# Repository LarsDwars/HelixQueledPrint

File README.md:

# HelixQueledPrint
An break out board and LED driver for RGBW LED's from the showtec helix s5000 or any queled Q4xx light

yay

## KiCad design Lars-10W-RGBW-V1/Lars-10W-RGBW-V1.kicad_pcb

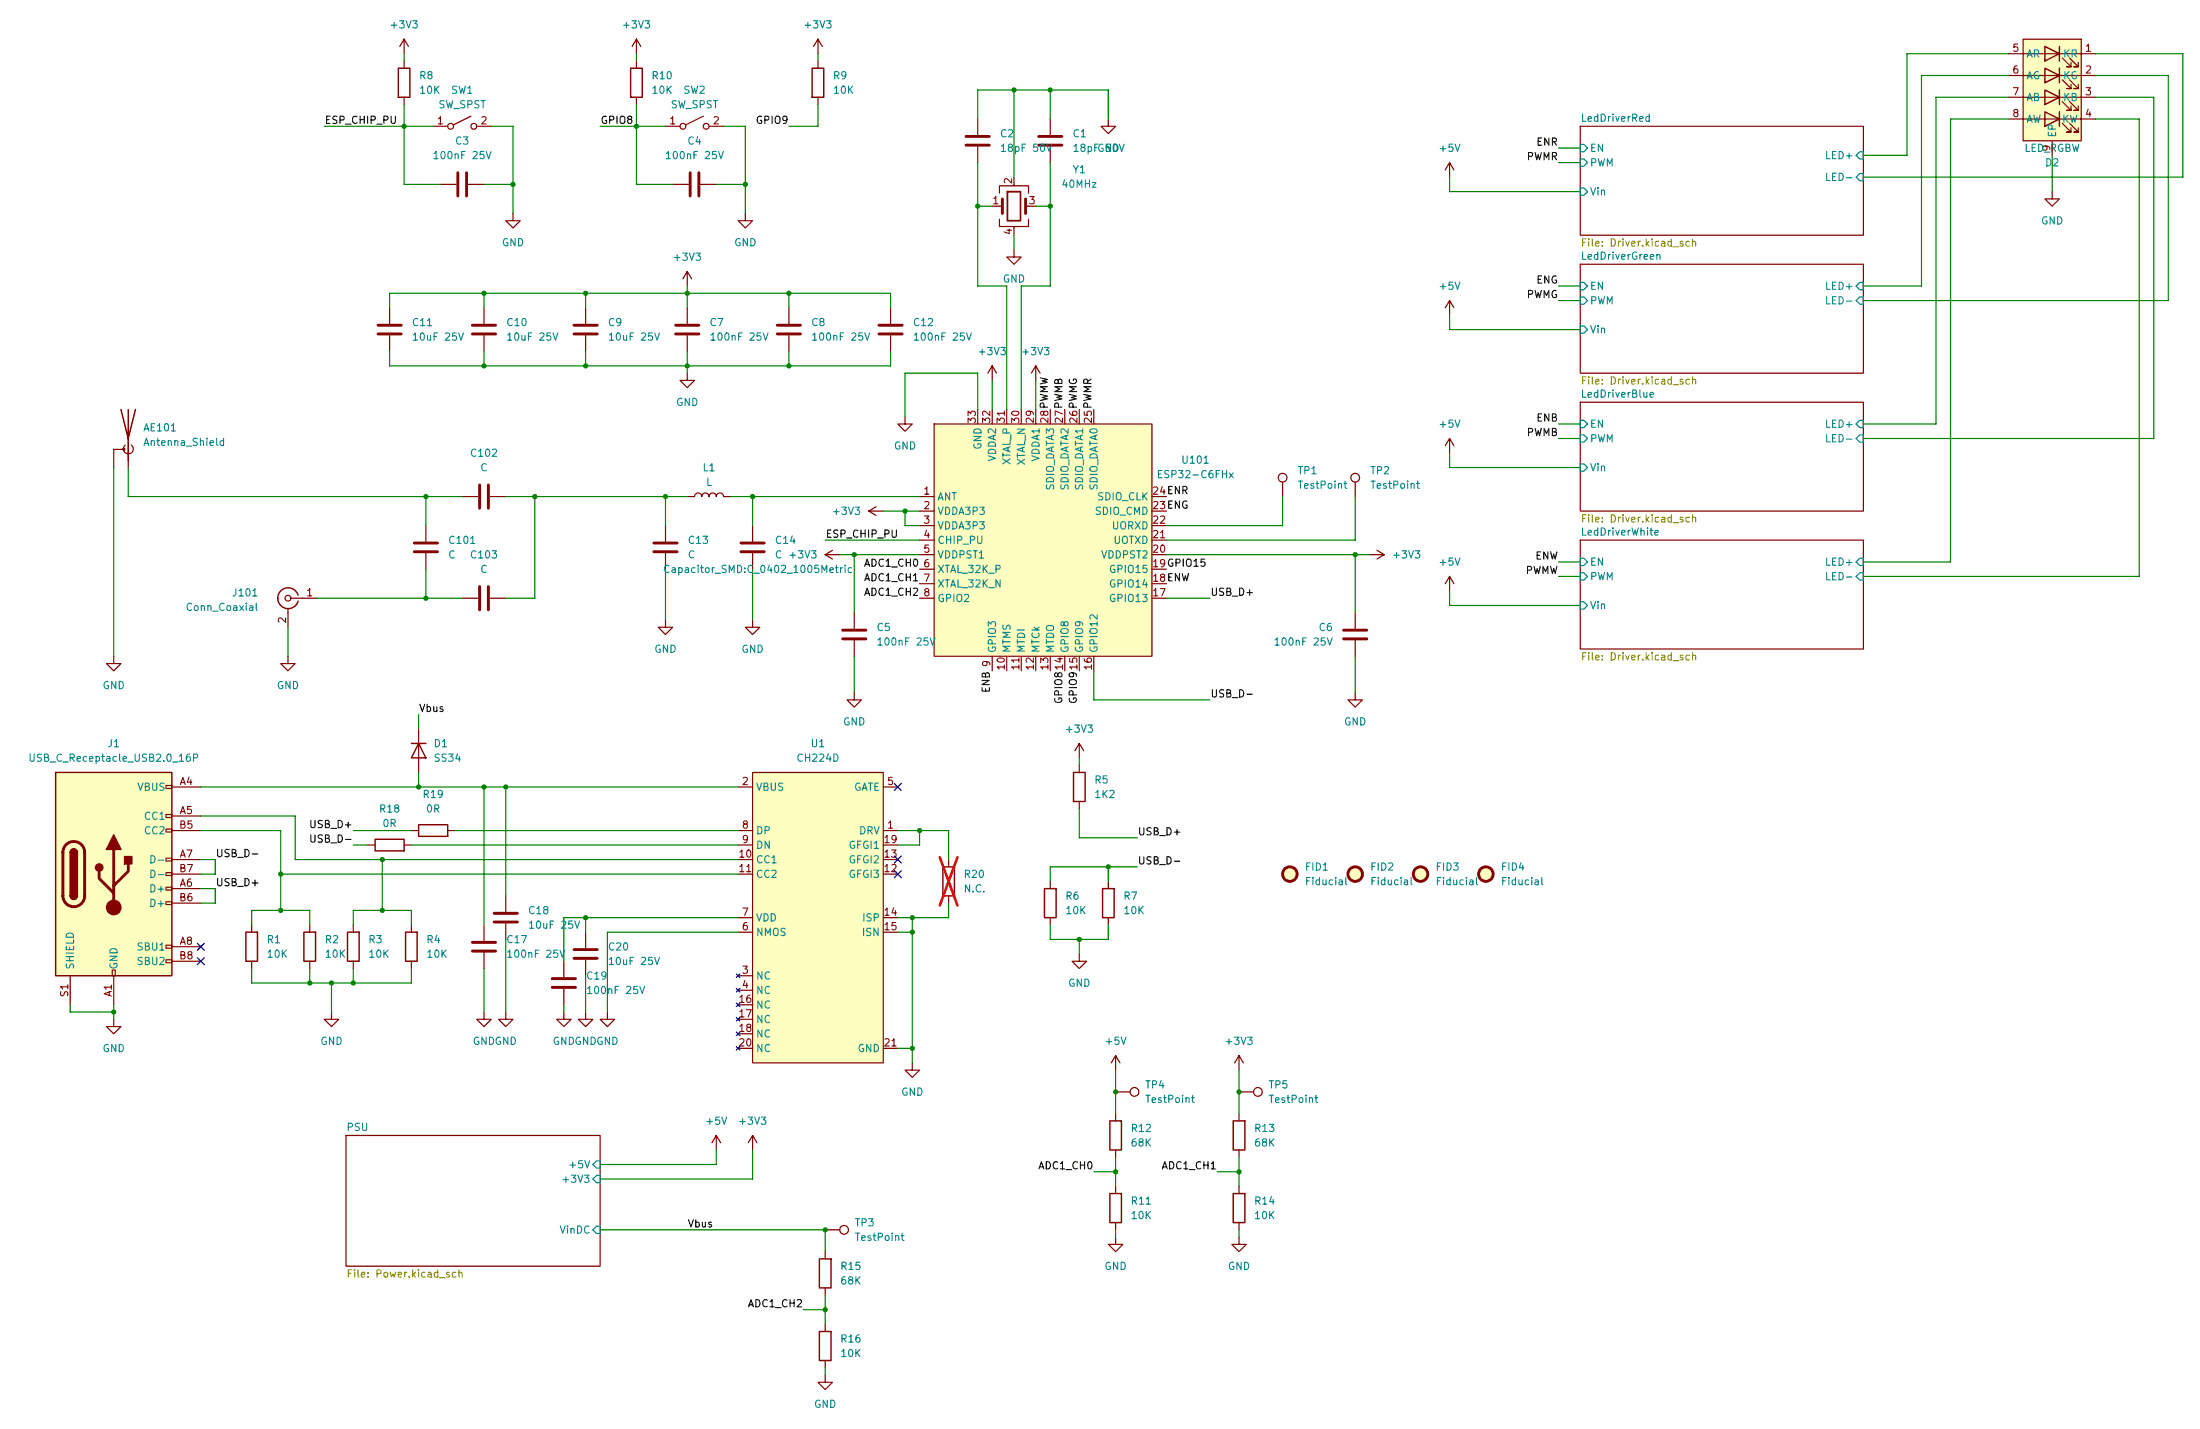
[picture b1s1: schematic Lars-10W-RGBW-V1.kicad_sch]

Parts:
AE101: Antenna_Shield; Texas_SWRA117D_2.4GHz_Right
C1, C2: 18pF 50V; C_0402_1005Metric
C3, C4, C5, C6, C7, C8, C12, C17, C19: 100nF 25V; C_0402_1005Metric
C9, C10, C11, C18, C20: 10uF 25V; C_0805_2012Metric
C13, C14, C101, C102, C103: C; C_0402_1005Metric
D1: SS34; SMA; MPN SS34
D2: LED_RGBW; QR4xLED
FID1, FID2, FID3, FID4: Fiducial; FIDUCIAL_Diameter_1mm
J1: USB_C_Receptacle_USB2.0_16P; USB_C_Receptacle_GCT_USB4105-xx-A_16P_TopMnt_Horizontal
J101: Conn_Coaxial; U.FL_Hirose_U.FL-R-SMT-1_Vertical; MPN RF1-2626-125CE-CT
L1: L; L_0402_1005Metric
R1, R2, R3, R4, R6, R7, R8, R9, R10, R11, R14, R16: 10K; R_0402_1005Metric
R5: 1K2; R_0402_1005Metric
R12, R13, R15: 68K; R_0402_1005Metric
R18, R19: 0R; R_0402_1005Metric
R20: N.C.; R_0402_1005Metric; not fitted
SW1, SW2: SW_SPST; TS1101A26025; MPN GT-TC034A-H025-L1NB
TP1, TP2, TP3, TP4, TP5: TestPoint; TestPoint_Pad_D1.0mm
U1: CH224D; QFN-20-1EP_3x3mm_P0.4mm_EP1.65x1.65mm_ThermalVias
U101: ESP32-C6FHx; QFN-32-1EP_5x5mm_P0.5mm_EP3.65x3.65mm_ThermalVias
Y1: 40MHz; Crystal_SMD_3225-4Pin_3.2x2.5mm_HandSoldering; MPN C37635388

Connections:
+3V3: C5.1, C6.1, C7.1, C8.1, C9.1, C10.1, C11.1, C12.1, R5.1, R8.1, R9.1, R10.1, R13.2, TP5.1, U101.2 (VDDA3P3), U101.3 (VDDA3P3), U101.5 (VDDPST1), U101.20 (VDDPST2), U101.29 (VDDA1), U101.32 (VDDA2); also elsewhere on the board
+5V: R12.2, TP4.1; also elsewhere on the board
/ADC1_CH0: R11.2, R12.1, U101.6 (XTAL_32K_P)
/ADC1_CH1: R13.1, R14.2, U101.7 (XTAL_32K_N)
/ADC1_CH2: R15.1, R16.2, U101.8 (GPIO2)
/ENB: U101.9 (GPIO3); also elsewhere on the board
/ENG: U101.23 (SDIO_CMD); also elsewhere on the board
/ENR: U101.24 (SDIO_CLK); also elsewhere on the board
/ENW: U101.18 (GPIO14); also elsewhere on the board
/ESP_CHIP_PU: C3.2, R8.2, SW1.1 (A), U101.4 (CHIP_PU)
/GPIO8: C4.2, R10.2, SW2.1 (A), U101.14 (GPIO8)
/GPIO9: R9.2, U101.15 (GPIO9)
/GPIO15: U101.19 (GPIO15)
/LedDriverBlue/LED+: D2.7 (AB); also elsewhere on the board
/LedDriverBlue/LED-: D2.3 (KB); also elsewhere on the board
/LedDriverGreen/LED+: D2.6 (AG); also elsewhere on the board
/LedDriverGreen/LED-: D2.2 (KG); also elsewhere on the board
/LedDriverRed/LED+: D2.5 (AR); also elsewhere on the board
/LedDriverRed/LED-: D2.1 (KR); also elsewhere on the board
/LedDriverWhite/LED+: D2.8 (AW); also elsewhere on the board
/LedDriverWhite/LED-: D2.4 (KW); also elsewhere on the board
/PWMB: U101.27 (SDIO_DATA2); also elsewhere on the board
/PWMG: U101.26 (SDIO_DATA1); also elsewhere on the board
/PWMR: U101.25 (SDIO_DATA0); also elsewhere on the board
/PWMW: U101.28 (SDIO_DATA3); also elsewhere on the board
/USB_D+: J1.A6 (D+), J1.B6 (D+), R5.2, R19.1, U101.17 (GPIO13)
/USB_D-: J1.A7 (D-), J1.B7 (D-), R6.2, R7.2, R18.1, U101.16 (GPIO12)
/Vbus: D1.1 (K), R15.2, TP3.1; also elsewhere on the board
GND: AE101.2 (Shield), C1.1, C2.1, C3.1, C4.1, C5.2, C6.2, C7.2, C8.2, C9.2, C10.2, C11.2, C12.2, C13.2, C14.2, C17.2, C18.2, C19.2, C20.2, D2.9 (EP), J1.A1 (GND), J1.A12 (GND), J1.B1 (GND), J1.B12 (GND), J1.S1 (SHIELD), J101.2 (Ext), R1.1, R2.1, R3.1, R4.1, R6.1, R7.1, R11.1, R14.1, R16.1, R20.2, SW1.2 (B), SW2.2 (B), U1.6 (NMOS), U1.14 (ISP), U1.15 (ISN), U1.21 (GND), U101.33 (GND), Y1.2, Y1.4; also elsewhere on the board
unnamed: AE101.1 (A), C101.1, C102.1
unnamed: C13.1, C102.2, C103.2, L1.1
unnamed: C17.1, C18.1, D1.2 (A), J1.A4 (VBUS), J1.A9 (VBUS), J1.B4 (VBUS), J1.B9 (VBUS), U1.2 (VBUS)
unnamed: J1.A5 (CC1), R3.2, R4.2, U1.10 (CC1)
unnamed: J1.B5 (CC2), R1.2, R2.2, U1.11 (CC2)
unnamed: C101.2, C103.1, J101.1 (In)
unnamed: R18.2, U1.9 (DN)
unnamed: R19.2, U1.8 (DP)
unnamed: R20.1, U1.1 (DRV), U1.19 (GFGI1)
unnamed: C19.1, C20.1, U1.7 (VDD)
unnamed: C14.1, L1.2, U101.1 (ANT)
unnamed: TP1.1, U101.22 (UORXD)
unnamed: TP2.1, U101.21 (UOTXD)
unnamed: C1.2, U101.30 (XTAL_N), Y1.3
unnamed: C2.2, U101.31 (XTAL_P), Y1.1

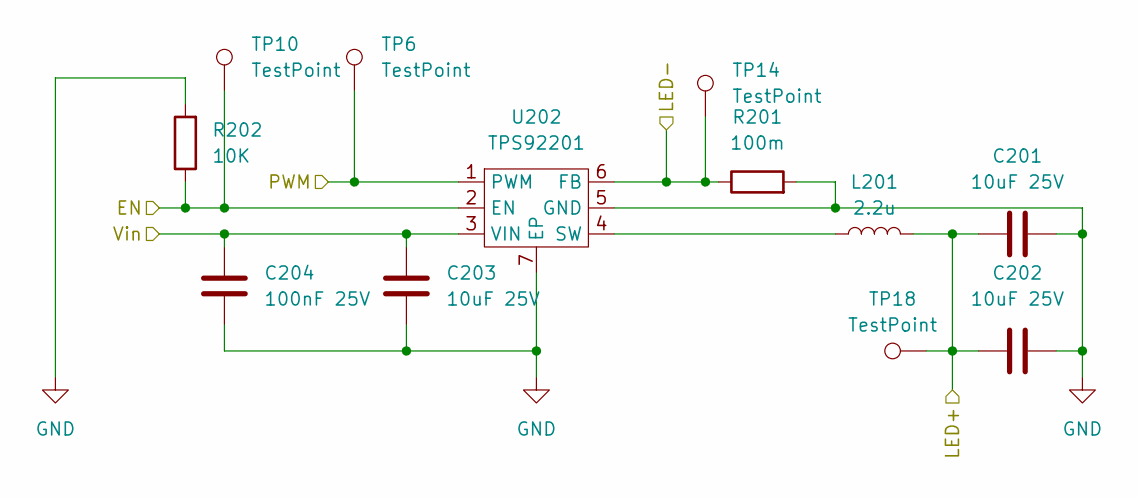
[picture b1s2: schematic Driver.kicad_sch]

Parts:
C201, C202, C203: 10uF 25V; C_0805_2012Metric
C204: 100nF 25V; C_0402_1005Metric
L201: 2.2u; L_APV_ANR4020; MPN SMNR4020-2.2UH
R201: 100m; R_0805_2012Metric
R202: 10K; R_0402_1005Metric
TP6, TP10, TP14, TP18: TestPoint; TestPoint_Pad_D1.0mm
U202: TPS92201; WSON-6-1EP_2x2mm_P0.65mm_EP1x1.6mm_ThermalVias

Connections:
+5V: C203.2, C204.2, U202.3 (VIN); also elsewhere on the board
/ENR: R202.1, TP10.1, U202.2 (EN); also elsewhere on the board
/LedDriverRed/LED+: C201.1, C202.1, L201.2, TP18.1; also elsewhere on the board
/LedDriverRed/LED-: R201.1, TP14.1, U202.6 (FB); also elsewhere on the board
/PWMR: TP6.1, U202.1 (PWM); also elsewhere on the board
GND: C201.2, C202.2, C203.1, C204.1, R201.2, R202.2, U202.5 (GND), U202.7 (EP); also elsewhere on the board
unnamed: L201.1, U202.4 (SW)

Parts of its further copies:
C301, C302, C303, C401, C402, C403, C501, C502, C503: 10uF 25V; C_0805_2012Metric
C304, C404, C504: 100nF 25V; C_0402_1005Metric
L301, L401, L501: 2.2u; L_APV_ANR4020; MPN SMNR4020-2.2UH
R301, R401, R501: 100m; R_0805_2012Metric
R302, R402, R502: 10K; R_0402_1005Metric
TP7, TP8, TP9, TP11, TP12, TP13, TP15, TP16, TP17, TP19, TP20, TP21: TestPoint; TestPoint_Pad_D1.0mm
U302, U402, U502: TPS92201; WSON-6-1EP_2x2mm_P0.65mm_EP1x1.6mm_ThermalVias

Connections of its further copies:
+5V: C303.2, C304.2, C403.2, C404.2, C503.2, C504.2, U302.3 (VIN), U402.3 (VIN), U502.3 (VIN); also elsewhere on the board
/ENB: R402.1, TP12.1, U402.2 (EN); also elsewhere on the board
/ENG: R302.1, TP11.1, U302.2 (EN); also elsewhere on the board
/ENW: R502.1, TP13.1, U502.2 (EN); also elsewhere on the board
/LedDriverBlue/LED+: C401.1, C402.1, L401.2, TP20.1; also elsewhere on the board
/LedDriverBlue/LED-: R401.1, TP16.1, U402.6 (FB); also elsewhere on the board
/LedDriverGreen/LED+: C301.1, C302.1, L301.2, TP19.1; also elsewhere on the board
/LedDriverGreen/LED-: R301.1, TP15.1, U302.6 (FB); also elsewhere on the board
/LedDriverWhite/LED+: C501.1, C502.1, L501.2, TP21.1; also elsewhere on the board
/LedDriverWhite/LED-: R501.1, TP17.1, U502.6 (FB); also elsewhere on the board
/PWMB: TP8.1, U402.1 (PWM); also elsewhere on the board
/PWMG: TP7.1, U302.1 (PWM); also elsewhere on the board
/PWMW: TP9.1, U502.1 (PWM); also elsewhere on the board
GND: C301.2, C302.2, C303.1, C304.1, C401.2, C402.2, C403.1, C404.1, C501.2, C502.2, C503.1, C504.1, R301.2, R302.2, R401.2, R402.2, R501.2, R502.2, U302.5 (GND), U302.7 (EP), U402.5 (GND), U402.7 (EP), U502.5 (GND), U502.7 (EP); also elsewhere on the board
unnamed: L301.1, U302.4 (SW)
unnamed: L401.1, U402.4 (SW)
unnamed: L501.1, U502.4 (SW)

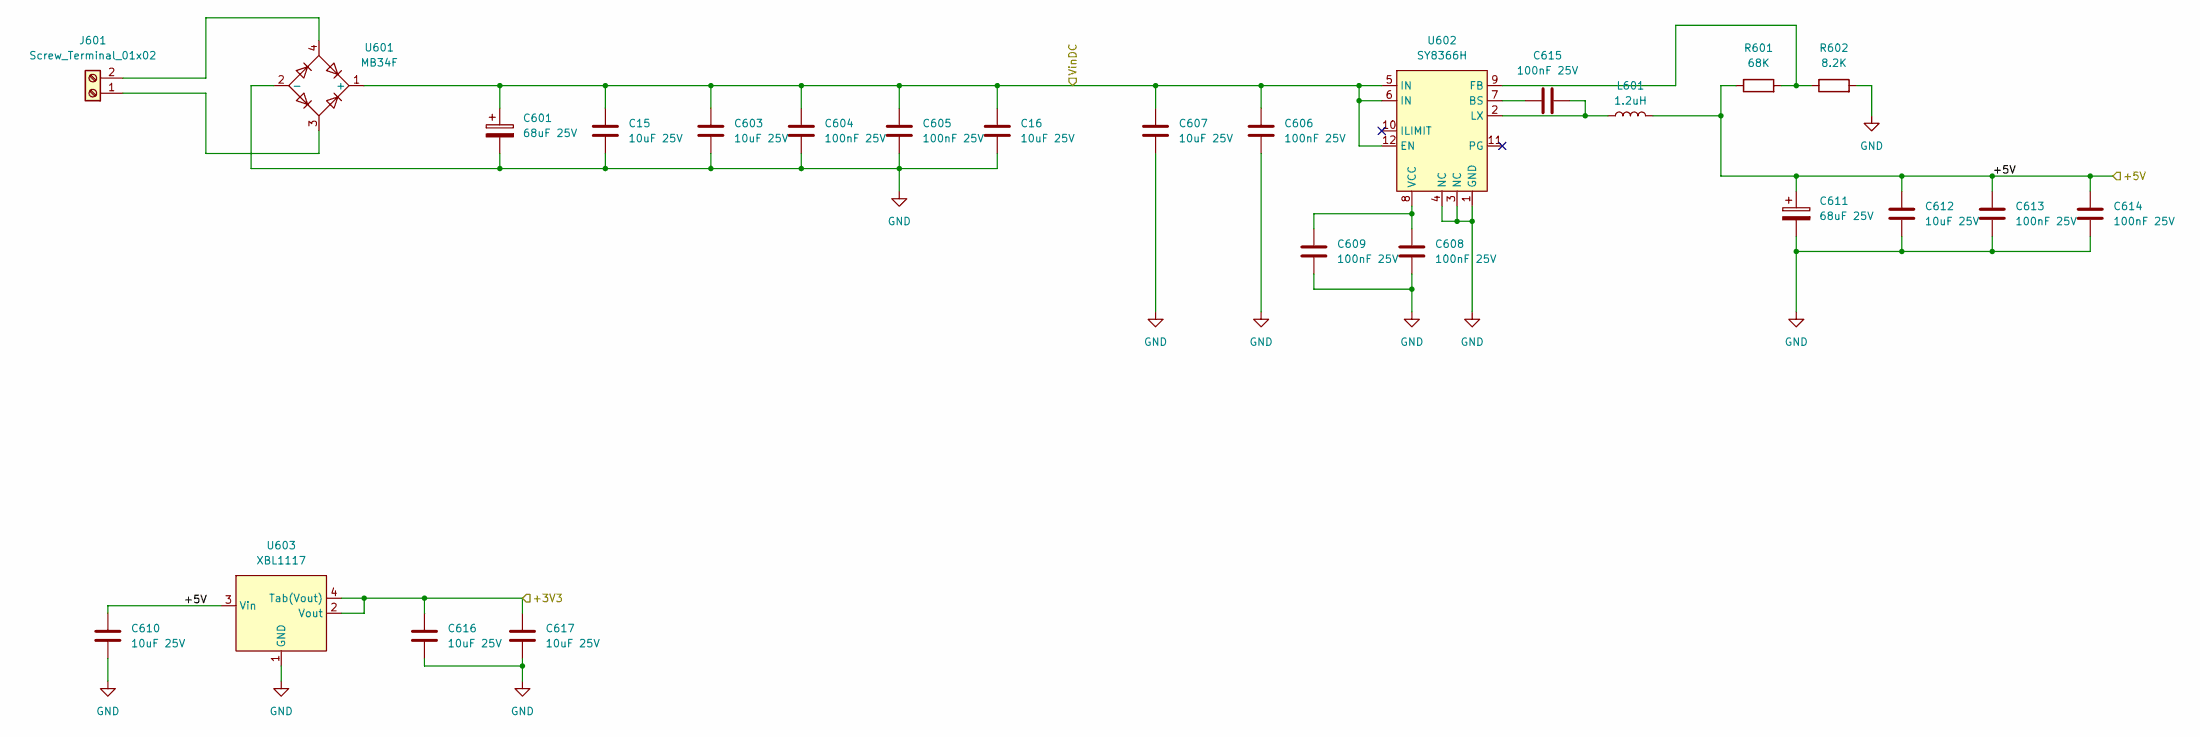
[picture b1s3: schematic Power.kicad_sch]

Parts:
C15, C16, C603, C607, C610, C612, C616, C617: 10uF 25V; C_0805_2012Metric
C601, C611: 68uF 25V; CP_Elec_6.3x5.4; MPN CS1E680M-CRE54
C604, C605, C606, C608, C609, C613, C614, C615: 100nF 25V; C_0402_1005Metric
J601: Screw_Terminal_01x02; TerminalBlock_Xinya_XY308-2.54-2P_1x02_P2.54mm_Horizontal; MPN MX128-2.54-02P-GN01-Cu-Y-A
L601: 1.2uH; L_APV_ANR4012; MPN FTC404020S1R2MBCA
R601: 68K; R_0402_1005Metric
R602: 8.2K; R_0402_1005Metric
U601: MB34F; MFB; MPN MB34F
U602: SY8366H; QFN3X3-12_SGY
U603: XBL1117; SOT-223; MPN XBLW XBL1117-3.3

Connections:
+3V3: C616.1, C617.1, U603.2 (Vout), U603.4 (Tab(Vout)); also elsewhere on the board
+5V: C610.1, C611.1, C612.1, C613.1, C614.1, L601.2, R601.1, U603.3 (Vin); also elsewhere on the board
/Vbus: C15.1, C16.1, C601.1, C603.1, C604.1, C605.1, C606.1, C607.1, U601.1 (+), U602.5 (IN), U602.6 (IN), U602.12 (EN); also elsewhere on the board
GND: C15.2, C16.2, C601.2, C603.2, C604.2, C605.2, C606.2, C607.2, C608.2, C609.2, C610.2, C611.2, C612.2, C613.2, C614.2, C616.2, C617.2, R602.2, U601.2 (-), U602.1 (GND), U602.3 (NC), U602.4 (NC), U603.1 (GND); also elsewhere on the board
unnamed: J601.1, U601.3
unnamed: J601.2, U601.4
unnamed: C615.1, U602.7 (BS)
unnamed: R601.2, R602.1, U602.9 (FB)
unnamed: C615.2, L601.1, U602.2 (LX)
unnamed: C608.1, C609.1, U602.8 (VCC)

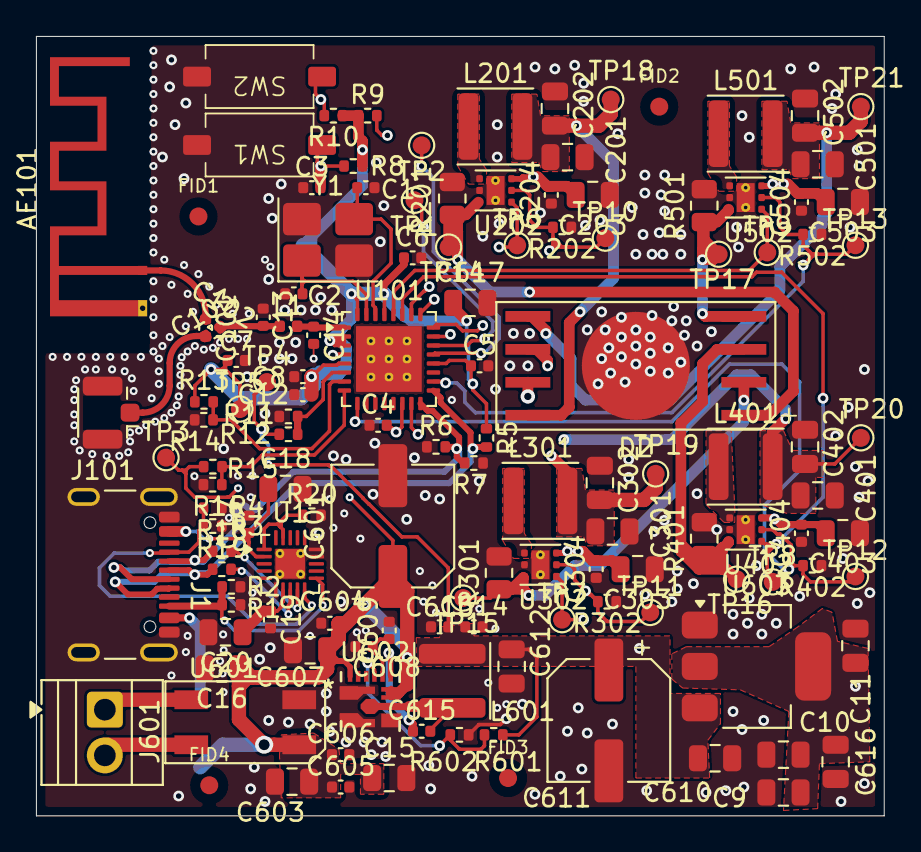
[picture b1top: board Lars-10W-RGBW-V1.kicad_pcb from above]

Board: 4 copper layers, 47.1 x 43.3 mm, 133 parts (1 on the bottom side), 53 nets.

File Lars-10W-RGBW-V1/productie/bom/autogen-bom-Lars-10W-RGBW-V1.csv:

This file is automatically generated. DO NOT EDIT!
"Qty";"Value";"Footprint";"Parts";"Description";"Type";"MPN";"Alternative";"Supplied by"

"2";"0R 1% 63mW";"R0402";"R18 R19";"Resistor";"smd";"";"";""
"4";"100m 1% 63mW";"R0402";"R201 R301 R401 R501";"Resistor";"smd";"";"";""
"1";"1K2 1% 63mW";"R0402";"R5";"Resistor";"smd";"";"";""
"1";"8.2K 1% 63mW";"R0402";"R602";"Resistor";"smd";"";"";""
"16";"10K 1% 63mW";"R0402";"R1 R2 R3 R4 R6 R7 R8 R9 R10 R11 R14 R16 R202 R302 R402 R502";"Resistor";"smd";"";"";""
"4";"68K 1% 63mW";"R0402";"R12 R13 R15 R601";"Resistor";"smd";"";"";""

"2";"18pF 50V C0G";"C0402";"C1 C2";"Unpolarized capacitor";"smd";"";"";""
"21";"100nF 25V X5R";"C0402";"C3 C4 C5 C6 C7 C8 C12 C17 C19 C204 C304 C404 C504 C604 C605 C606 C608 C609 C613 C614 C615";"Unpolarized capacitor";"smd";"";"";""
"5";"C";"C0402";"C13 C14 C101 C102 C103";"Unpolarized capacitor";"smd";"";"";""
"25";"10uF 25V X5R";"C0805";"C9 C10 C11 C15 C16 C18 C20 C201 C202 C203 C301 C302 C303 C401 C402 C403 C501 C502 C503 C603 C607 C610 C612 C616 C617";"Unpolarized capacitor";"smd";"";"";""
"2";"68uF 25V";"CP_Elec_6.3x5.4";"C601 C611";"Polarized capacitor";"smd";"CS1E680M-CRE54 ";"";""

"1";"1.2uH";"L_APV_ANR4012";"L601";"Inductor";"smd";"FTC404020S1R2MBCA";"";""
"4";"2.2u";"L_APV_ANR4020";"L201 L301 L401 L501";"Inductor";"smd";"SMNR4020-2.2UH";"";""
"1";"L";"L0402";"L1";"Inductor";"smd";"";"";""

"1";"LED_RGBW";"QR4xLED";"D2";"";"smd";"";"";""
"1";"SS34";"SMA";"D1";"Diode";"smd";"SS34";"";""

"1";"Antenna_Shield";"Texas_SWRA117D_2.4GHz_Right";"AE101";"Antenna with extra pin for shielding";"conventional";"";"";""

"1";"Conn_Coaxial";"U.FL_Hirose_U.FL-R-SMT-1_Vertical";"J101";"coaxial connector (BNC, SMA, SMB, SMC, Cinch/RCA, LEMO, ...)";"smd";"RF1-2626-125CE-CT";"";""
"1";"Screw_Terminal_01x02";"TerminalBlock_Xinya_XY308-2.54-2P_1x02_P2.54mm_Horizontal";"J601";"Generic screw terminal, single row, 01x02, script generated (kicad-library-utils/schlib/autogen/connector/)";"conventional";"MX128-2.54-02P-GN01-Cu-Y-A ";"";""
"1";"USB_C_Receptacle_USB2.0_16P";"USB_C_Receptacle_GCT_USB4105-xx-A_16P_TopMnt_Horizontal";"J1";"USB 2.0-only 16P Type-C Receptacle connector";"conventional";"";"";""

"2";"SW_SPST";"TS1101A26025";"SW1 SW2";"Single Pole Single Throw (SPST) switch";"smd";"GT-TC034A-H025-L1NB";"";""

"1";"CH224D";"QFN-20-1EP_3x3mm_P0.4mm_EP1.65x1.65mm_ThermalVias";"U1";"";"conventional";"";"";""
"1";"ESP32-C6FHx";"QFN-32-1EP_5x5mm_P0.5mm_EP3.65x3.65mm_ThermalVias";"U101";"";"conventional";"";"";""
"1";"MB34F";"MFB";"U601";"Full bridge rectifier 200V 3A";"smd";"MB34F";"";""
"1";"SY8366H";"QFN3X3-12_SGY";"U602";"";"smd";"";"";""
"4";"TPS92201";"WSON-6-1EP_2x2mm_P0.65mm_EP1x1.6mm_ThermalVias";"U202 U302 U402 U502";"";"conventional";"";"";""
"1";"XBL1117";"SOT-223";"U603";"";"smd";"XBLW XBL1117-3.3";"";""

"1";"40MHz";"Crystal_SMD_3225-4Pin_3.2x2.5mm_HandSoldering";"Y1";"Four pin crystal, GND on pins 2 and 4";"smd";"C37635388";"";""

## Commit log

2025-08-11 creating project
2025-08-11 (S)Created led drivers, started MCU design
2025-08-12 5V Voeding toegevoegd
2025-08-12 3.3V voeding toegevoegd
2025-08-12 USB-c en boot/reset knoppen toegevoegd
2025-08-13 GPIO verbindingen gemaakt, en condensatoren toegevoegd
2025-08-13 footprints toegewezen
2025-08-13 Netklases toegevoegd, componenten naar pcb geplaatst
2025-08-28 Update na spanje vakantie
2025-09-07 added some stuffs
2025-12-20 Alles afgerond, geen drc errors meer
2025-12-21 kleine aanpassingen
2025-12-22 added usb-pd trigger
2025-12-22 finished (i think)
2025-12-24 added fiducials, fixed shunt resistor size
2025-12-26 fixed rf path
2025-12-27 fixed led polarity
2025-12-29 finishing touches
2025-12-29 V1 exported, and ordered. DO NOT EDIT renamed tree, fixed stackup data.
2025-12-31 Fixed via sizes
